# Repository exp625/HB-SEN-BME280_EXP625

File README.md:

# HB-SEN-BME280_EXP625

**PCB for DIY AsksinPP++ Temperature/Humidity/Pressure sensor based on a BOSCH BME280 sensor and an Arduino Pro Mini**

## Credits

- This PCB is derived from FUEL4LP's PCB [HB-UNI-SEN-BATT_FUEL4EP](https://github.com/FUEL4EP/HomeAutomation/tree/master/AsksinPP_developments/PCBs/HB-UNI-SEN-BATT_FUEL4EP) and [HB-UNI-SEN-BATT_ATMega1284P_E07-868MS10_FRAM_FUEL4EP ](https://github.com/FUEL4EP/HomeAutomation/tree/master/AsksinPP_developments/PCBs/HB-UNI-SEN-BATT_ATMega1284P_E07-868MS10_FRAM_FUEL4EP).

## Changes

- Smaller PCB footprint to fit into the CBRS02VWH case
- surface mount assembly of the arduino and c1101 module to save space
- specific to one bme280 chip, everything else removed
- additional reset button, because the onboard reset button of the arduino needs to be removed due to the height.

## Hands-on test

The provided gerber files were used to order the pcb from JLCPCB and assemble 4 sensors, which are working perfectly for some time now

## Part List

| Count | Part                 | Label      |
|-------|----------------------|------------|
| 1     | IRLU024N             | Q1         |
| 2     | Resistor 100 kOhm    | R1,R5      |
| 1     | Resistor 470 Ohm     | R2         |
| 2     | Resistor 10 kOhm     | R3,R4      |
| 1     | Resistor 220 kOhm    | R6         |
| 1     | 10uF RM 1.5          | C1         |
| 3     | 6 Pin Jumper 2.54mm  | J1, J2, J3 |
| 2     | Battery Holder 6S-AA | BT1, BT2   |
| 1     | Arduino Pro Mini     | U1         |
| 1     | C1101 RF Module      | U2         |
| 1     | BME280 3.3V Devboard | U3         |
| 1     | Red 3mm LED          | D1         |
| 2     | Button 6x6mm         | SW1,SW2    |

Remove onboard leds, button and voltage regulator from the arduino board.

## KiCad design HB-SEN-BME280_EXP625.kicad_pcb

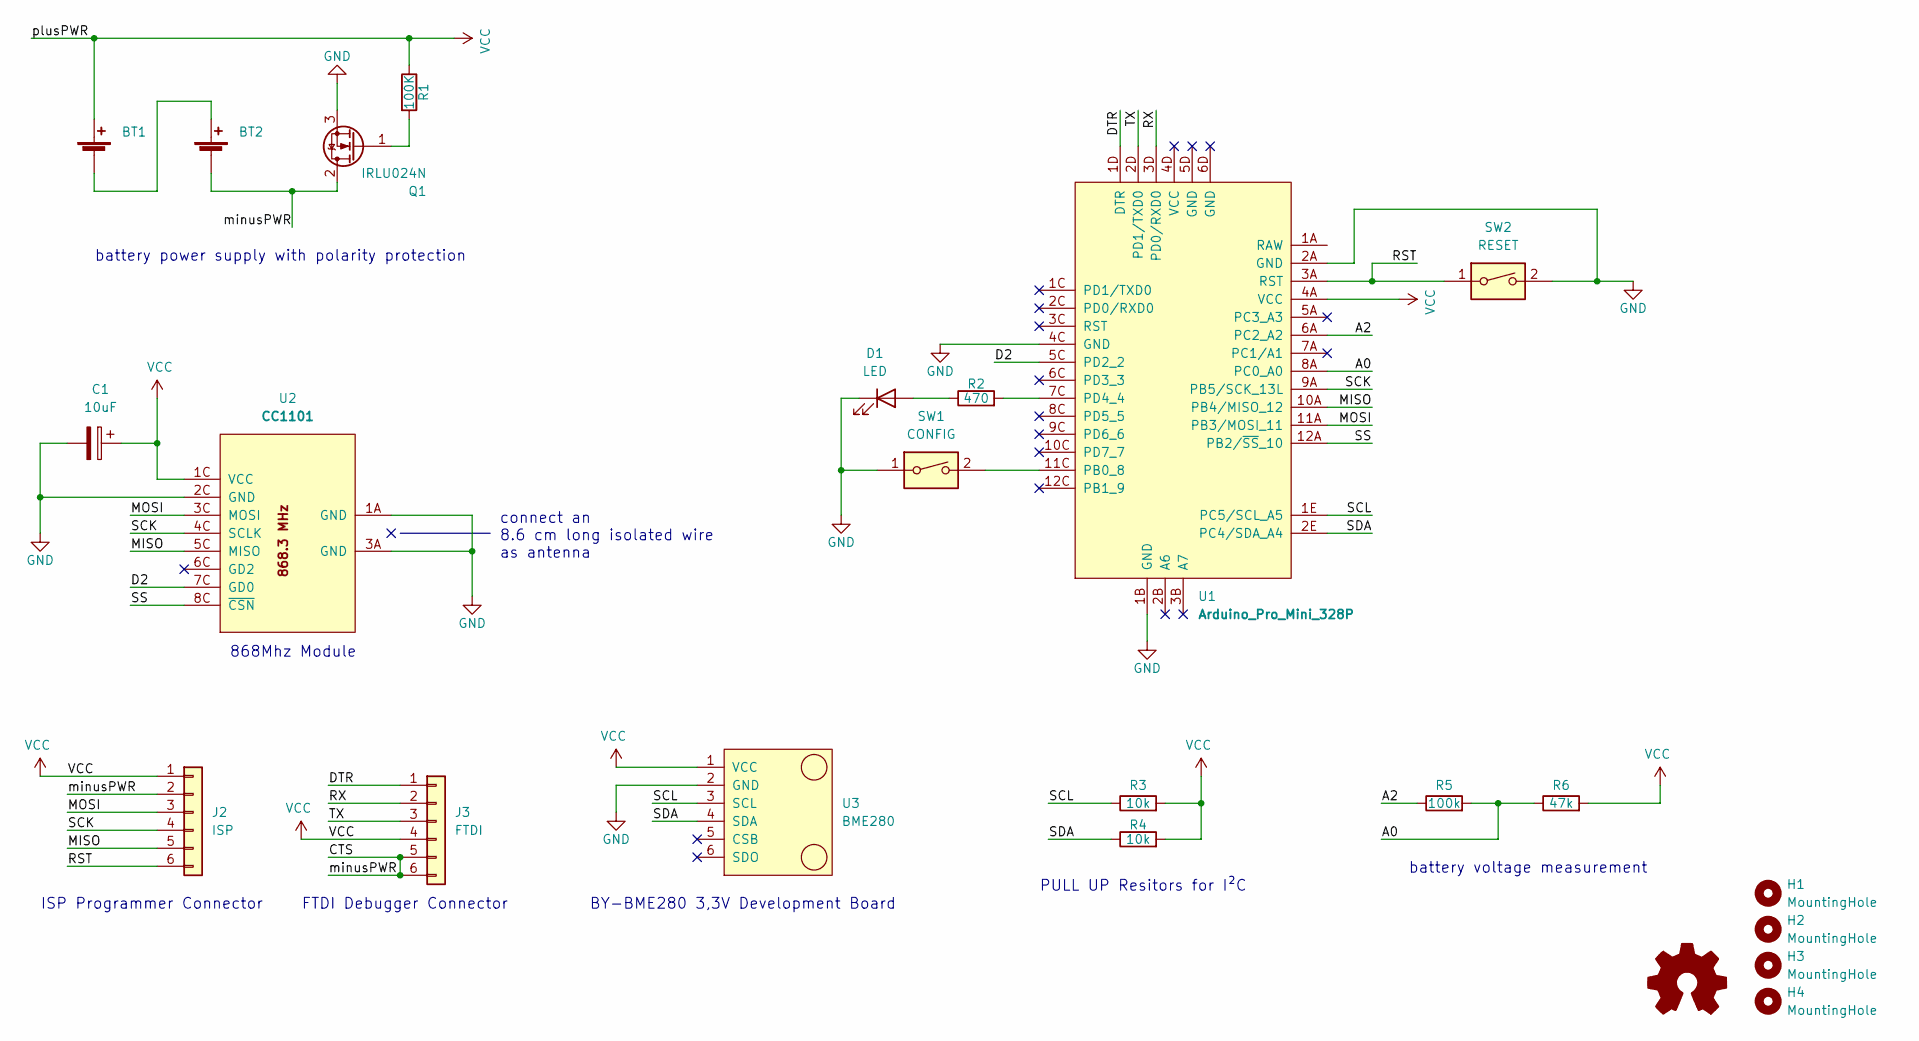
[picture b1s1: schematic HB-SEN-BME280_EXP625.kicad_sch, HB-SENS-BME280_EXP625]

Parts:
BT1, BT2: (no value)
C1: 10uF; CP_Radial_D4.0mm_P1.50mm
D1: LED; LED_D3.0mm
H1, H2, H3, H4: MountingHole; MountingHole_2.2mm_M2_Pad_Via
J2: ISP; PinHeader_1x06_P2.54mm_Vertical
J3: FTDI; PinHeader_1x06_P2.54mm_Vertical
LOGO1: Logo_Open_Hardware_Small; CC-BY-ND-SA; JLCPCB BOM 0
Q1: IRLU024N; TO-251-3_Vertical
R1: 100K; R_Axial_DIN0207_L6.3mm_D2.5mm_P2.54mm_Vertical
R2: 470; R_Axial_DIN0207_L6.3mm_D2.5mm_P2.54mm_Vertical
R3, R4: 10k; R_Axial_DIN0207_L6.3mm_D2.5mm_P2.54mm_Vertical
R5: 100k; R_Axial_DIN0207_L6.3mm_D2.5mm_P2.54mm_Vertical
R6: 47k; R_Axial_DIN0207_L6.3mm_D2.5mm_P2.54mm_Vertical
SW1: CONFIG; SW_PUSH_6mm_H5mm
SW2: RESET; SW_PUSH_6mm_H5mm
U1: Arduino_Pro_Mini_328P; ArduinoProMini
U2: CC1101
U3: BME280; module_bme280

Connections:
/A0: R5.2, R6.1, U1.8A (PC0_A0)
/A2: R5.1, U1.6A (PC2_A2)
/CTS: BT2.2 (-), J2.2, J3.5, J3.6, Q1.2 (D)
/D2: U1.5C (PD2_2), U2.7C (GD0)
/DTR: J3.1, U1.1D (DTR)
/MISO: J2.5, U1.10A (PB4/MISO_12), U2.5C (MISO)
/MOSI: J2.3, U1.11A (PB3/MOSI_11), U2.3C (MOSI)
/RST: J2.6, SW2.1, U1.3A (RST)
/RX: J3.2, U1.3D (PD0/RXD0)
/SCK: J2.4, U1.9A (PB5/SCK_13L), U2.4C (SCLK)
/SCL: R3.1, U1.1E (PC5/SCL_A5), U3.3 (SCL)
/SDA: R4.1, U1.2E (PC4/SDA_A4), U3.4 (SDA)
/SS: U1.12A (PB2/~SS_10), U2.8C (~CSN)
/TX: J3.3, U1.2D (PD1/TXD0)
GND: C1.2, D1.1 (K), Q1.3 (S), SW1.1, SW2.2, U1.1B (GND), U1.2A (GND), U1.4C (GND), U2.1A (GND), U2.2C (GND), U2.3A (GND), U3.2 (GND)
unnamed: BT1.2 (-), BT2.1 (+)
unnamed: D1.2 (A), R2.1
unnamed: Q1.1 (G), R1.2
unnamed: R2.2, U1.7C (PD4_4)
unnamed: SW1.2, U1.11C (PB0_8)
VCC: BT1.1 (+), C1.1, J2.1, J3.4, R1.1, R3.2, R4.2, R6.2, U1.4A (VCC), U2.1C (VCC), U3.1 (VCC)

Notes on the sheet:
connect an 8.6 cm long isolated wire as antenna
battery power supply with polarity protection
BY-BME280 3,3V Development Board
PULL UP Resitors for I²C
battery voltage measurement
FTDI Debugger Connector
ISP Programmer Connector
868Mhz Module

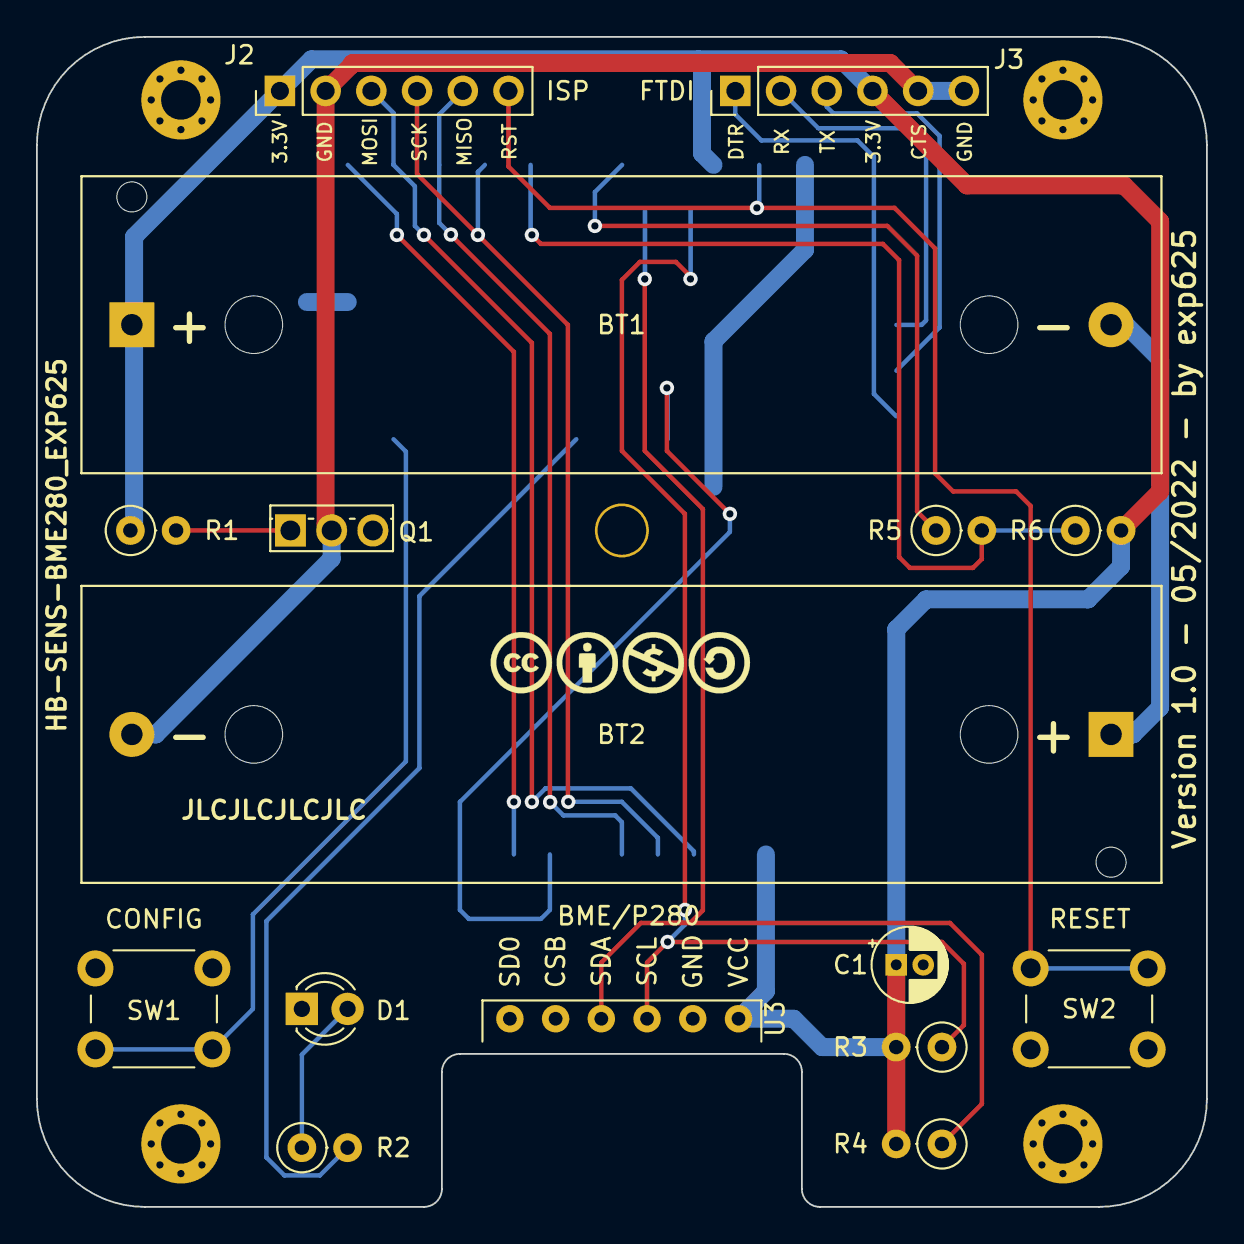
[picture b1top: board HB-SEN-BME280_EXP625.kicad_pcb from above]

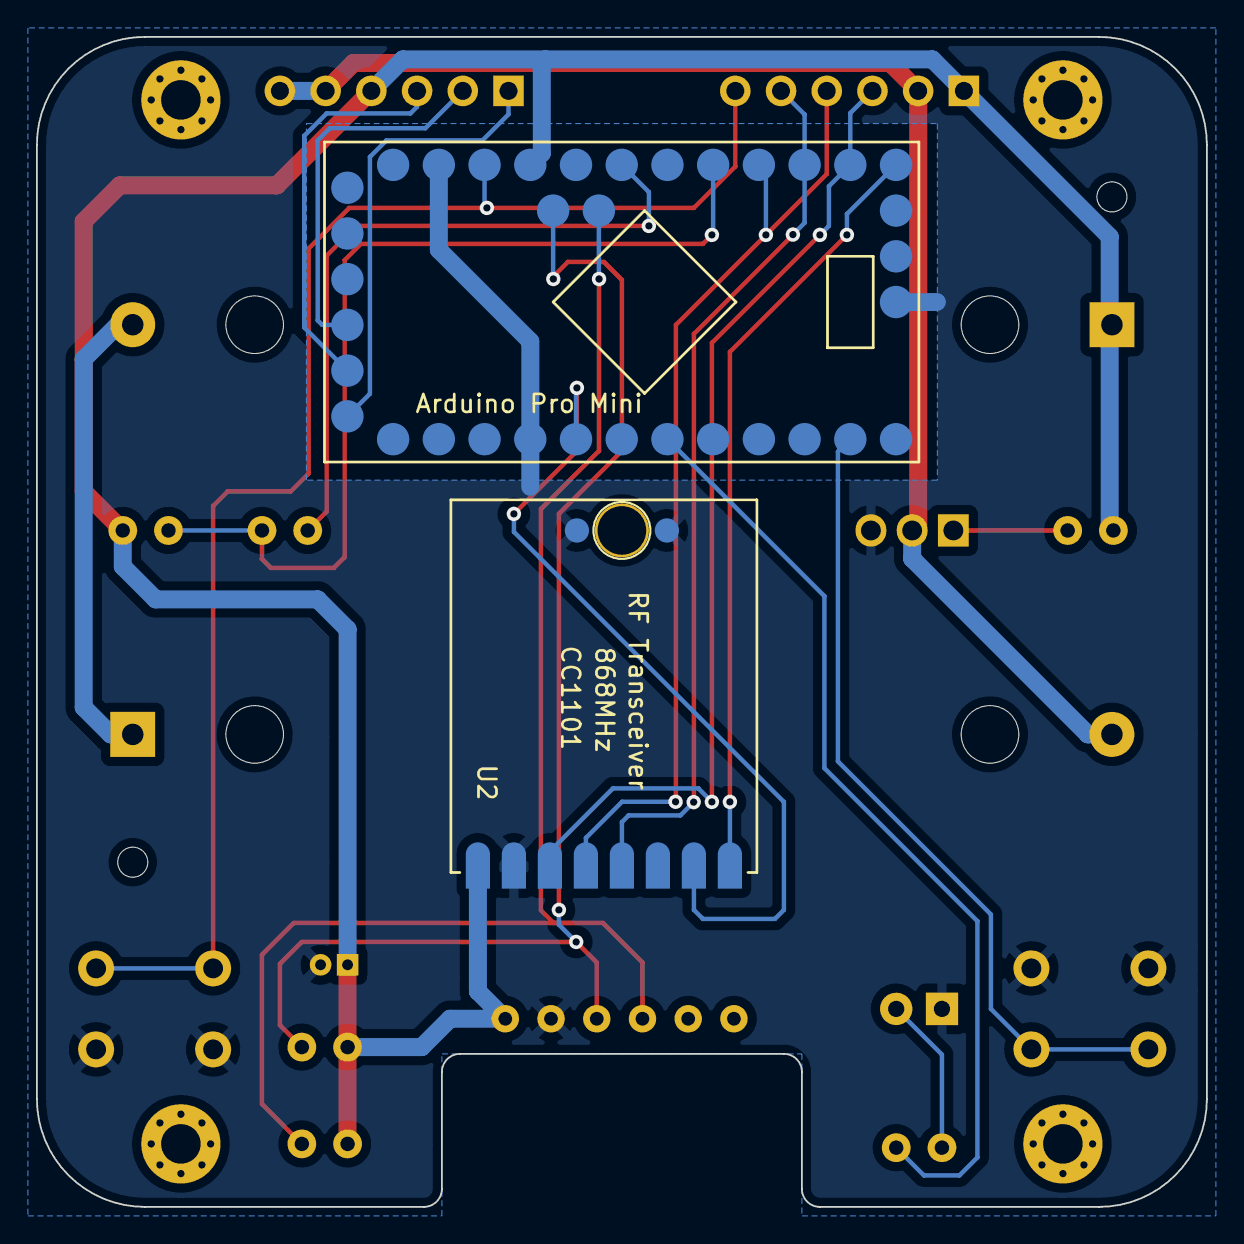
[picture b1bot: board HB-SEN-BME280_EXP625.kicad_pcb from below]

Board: 2 copper layers, 65.0 x 65.0 mm, 23 parts (2 on the bottom side), 21 nets.

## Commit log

2022-05-02 :sparkles: Revision 1.0
    :sparkles: Revision 1.0 with Keystone 2460 / Goobay AA battery holder
    :sparkles: Revision 1.0
2022-05-22 :bug: Fix resistor value in voltage divider
2022-05-23 :memo: Add README
2022-05-23 :pencil2: Fix typos
2022-05-23 :page_facing_up: Add LICENSE.md

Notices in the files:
HB-SEN-BME280_EXP625.kicad_pcb:
Creative Commons License, non-commercial
README.md:
License: CC BY-NC-SA 4.0
